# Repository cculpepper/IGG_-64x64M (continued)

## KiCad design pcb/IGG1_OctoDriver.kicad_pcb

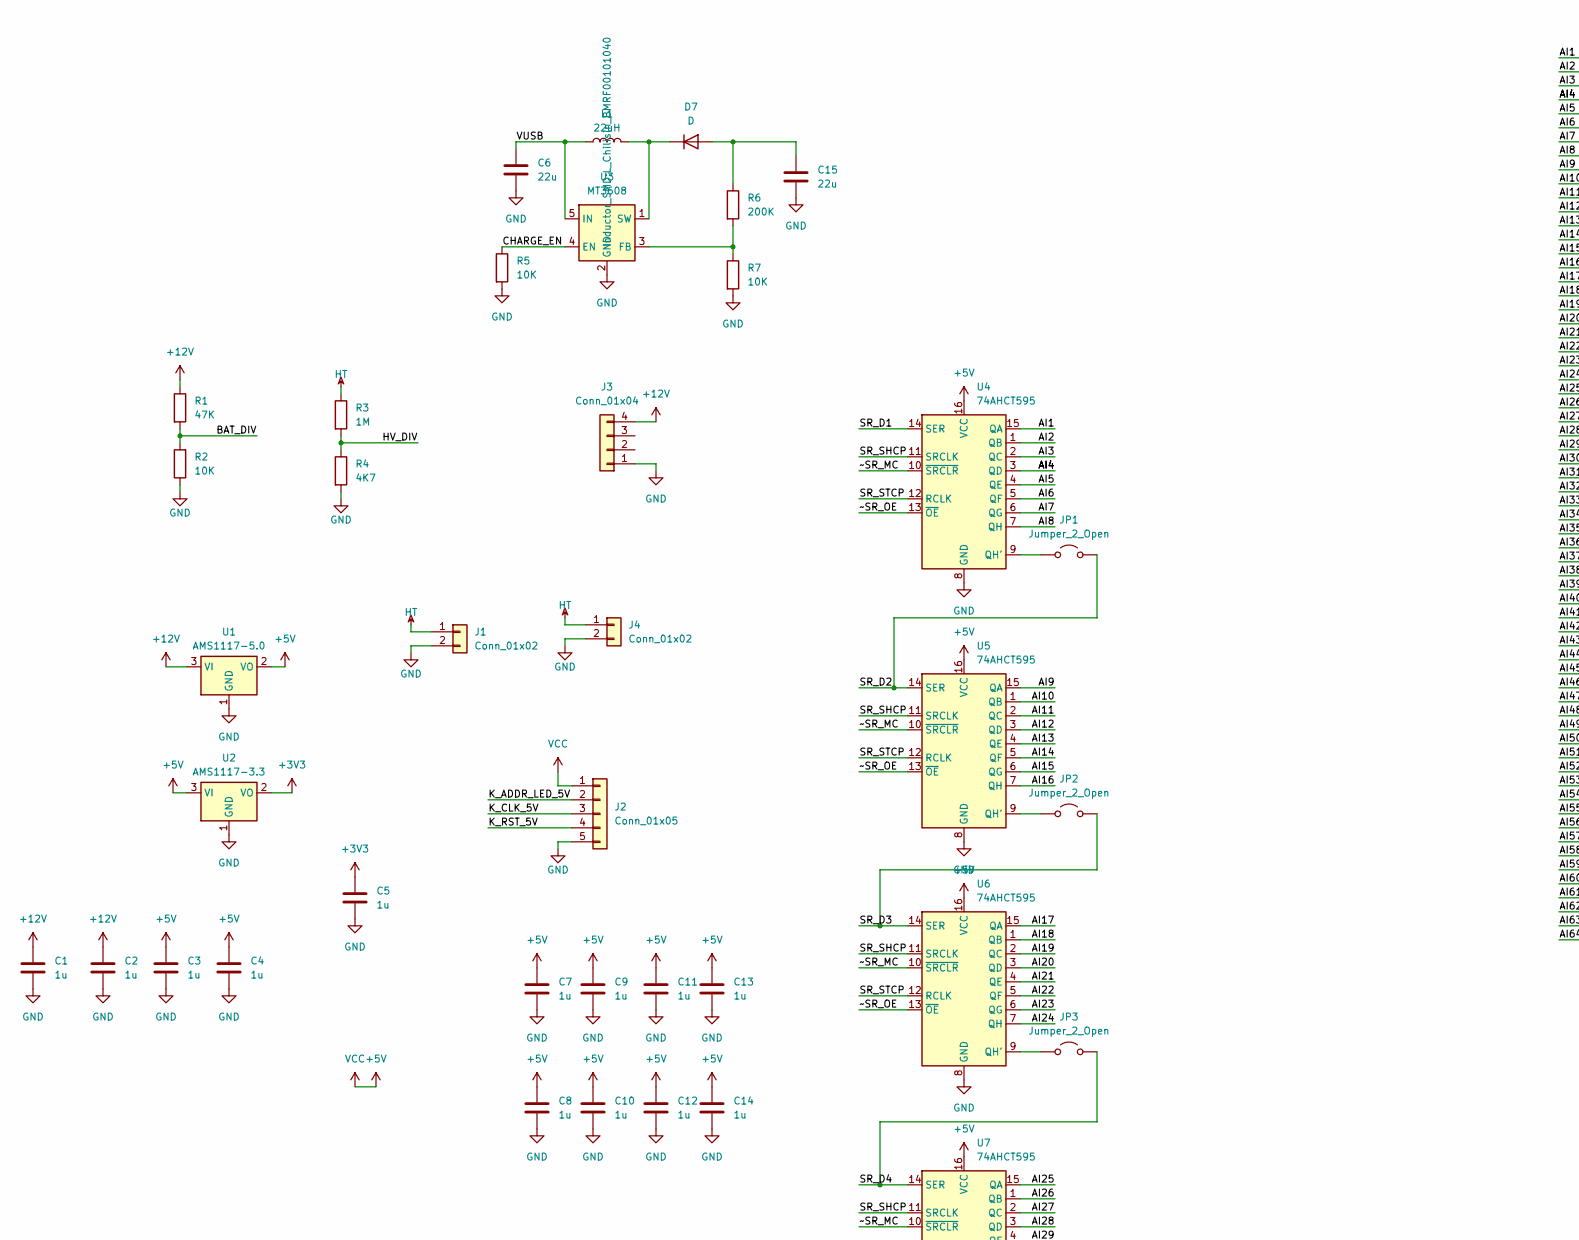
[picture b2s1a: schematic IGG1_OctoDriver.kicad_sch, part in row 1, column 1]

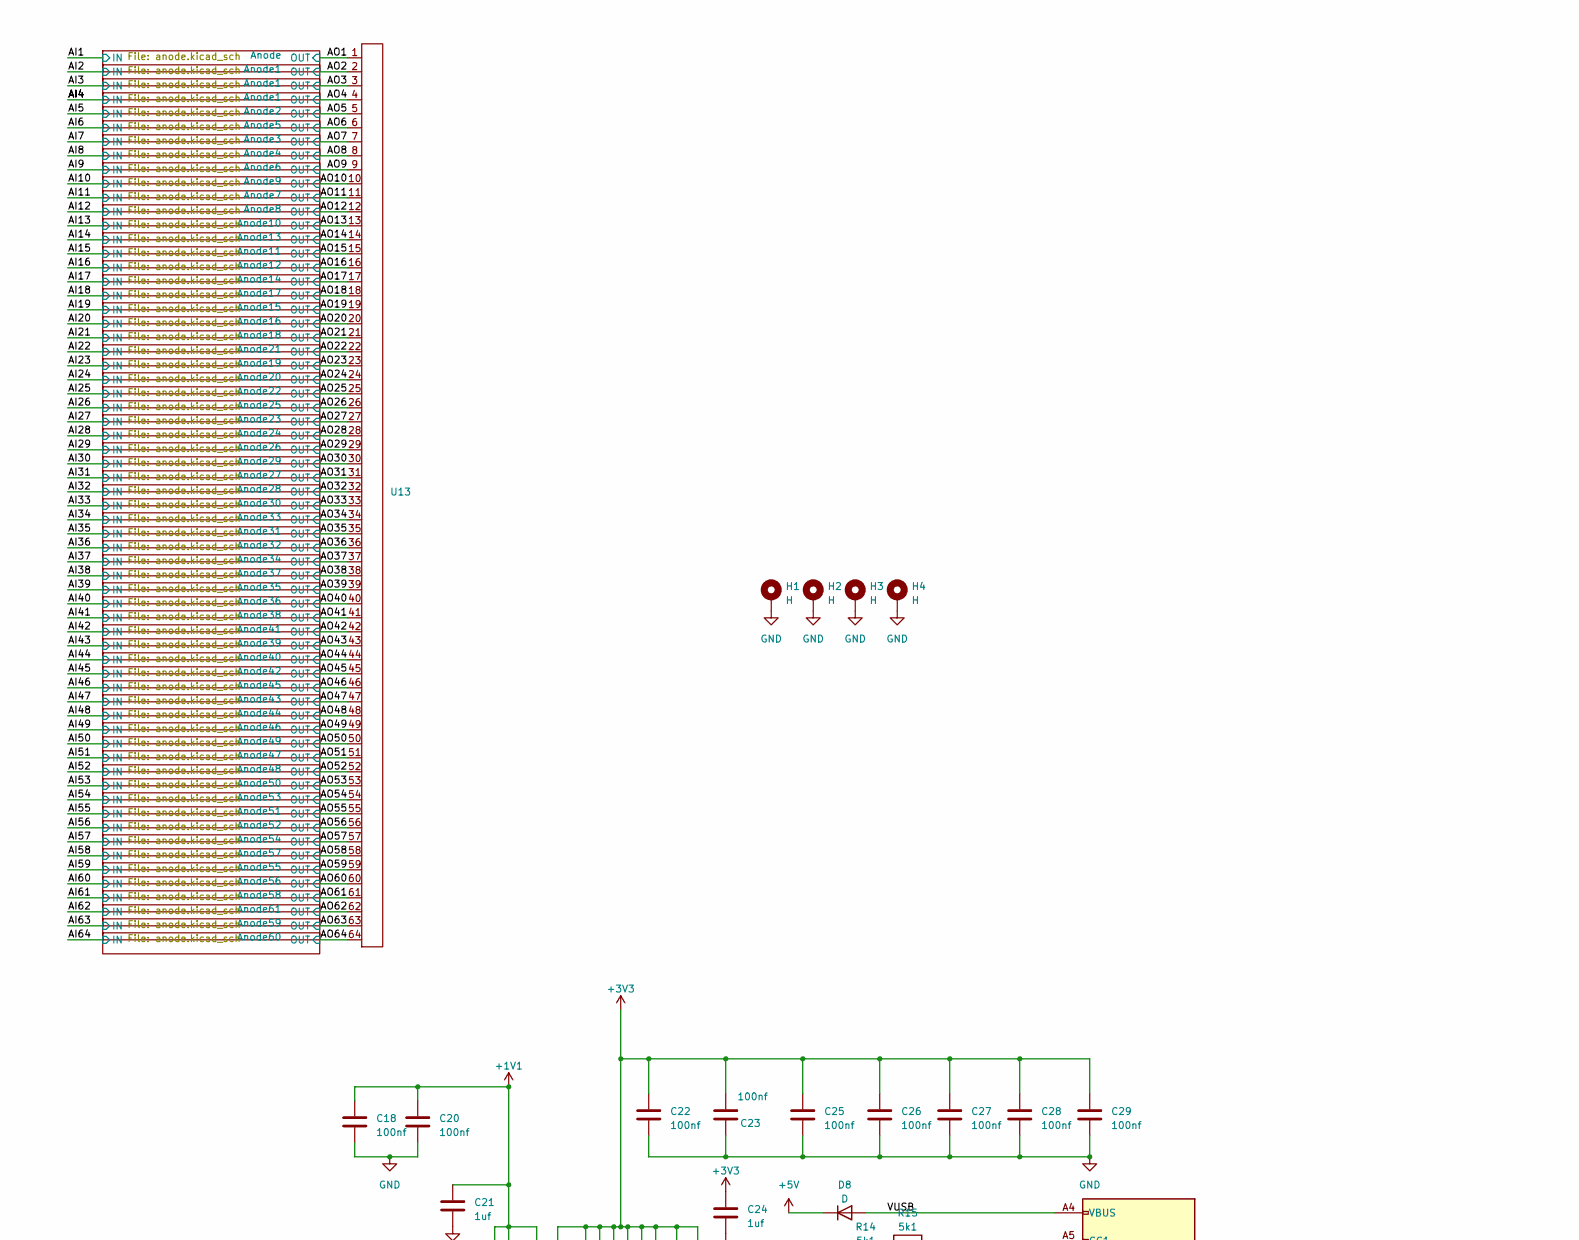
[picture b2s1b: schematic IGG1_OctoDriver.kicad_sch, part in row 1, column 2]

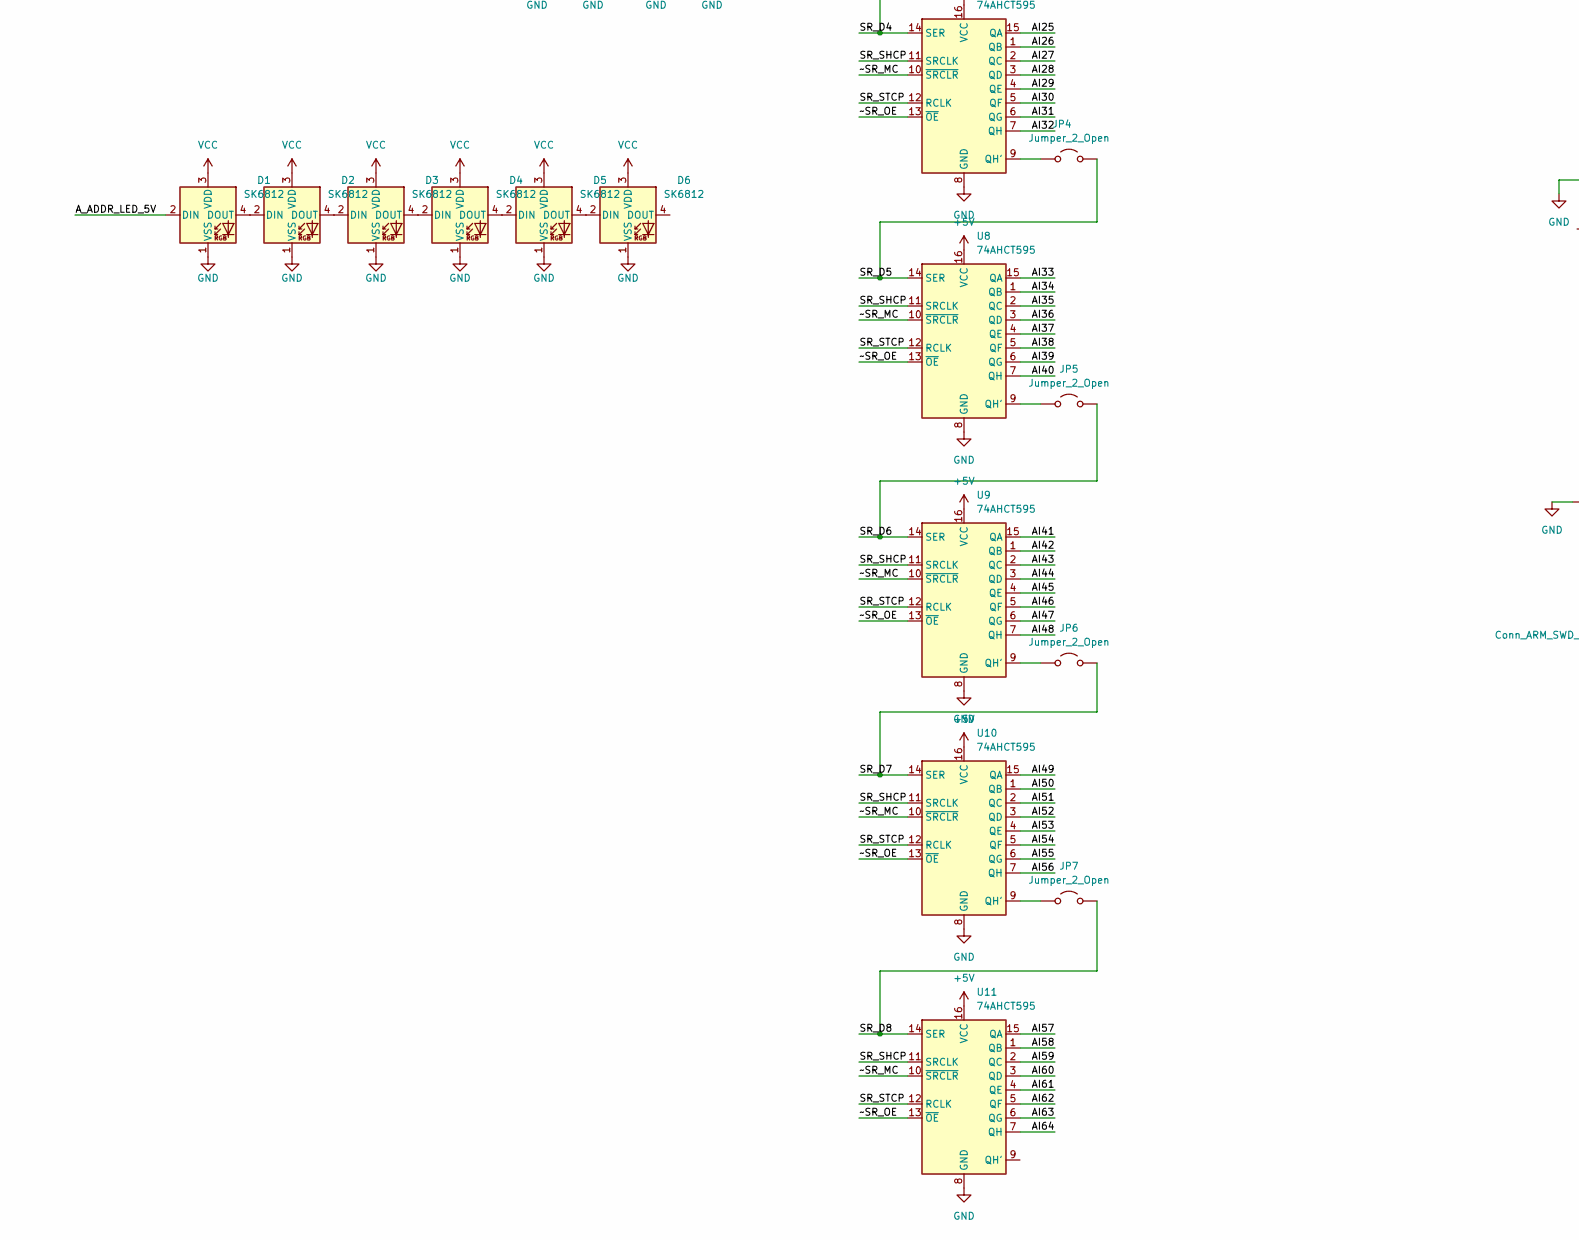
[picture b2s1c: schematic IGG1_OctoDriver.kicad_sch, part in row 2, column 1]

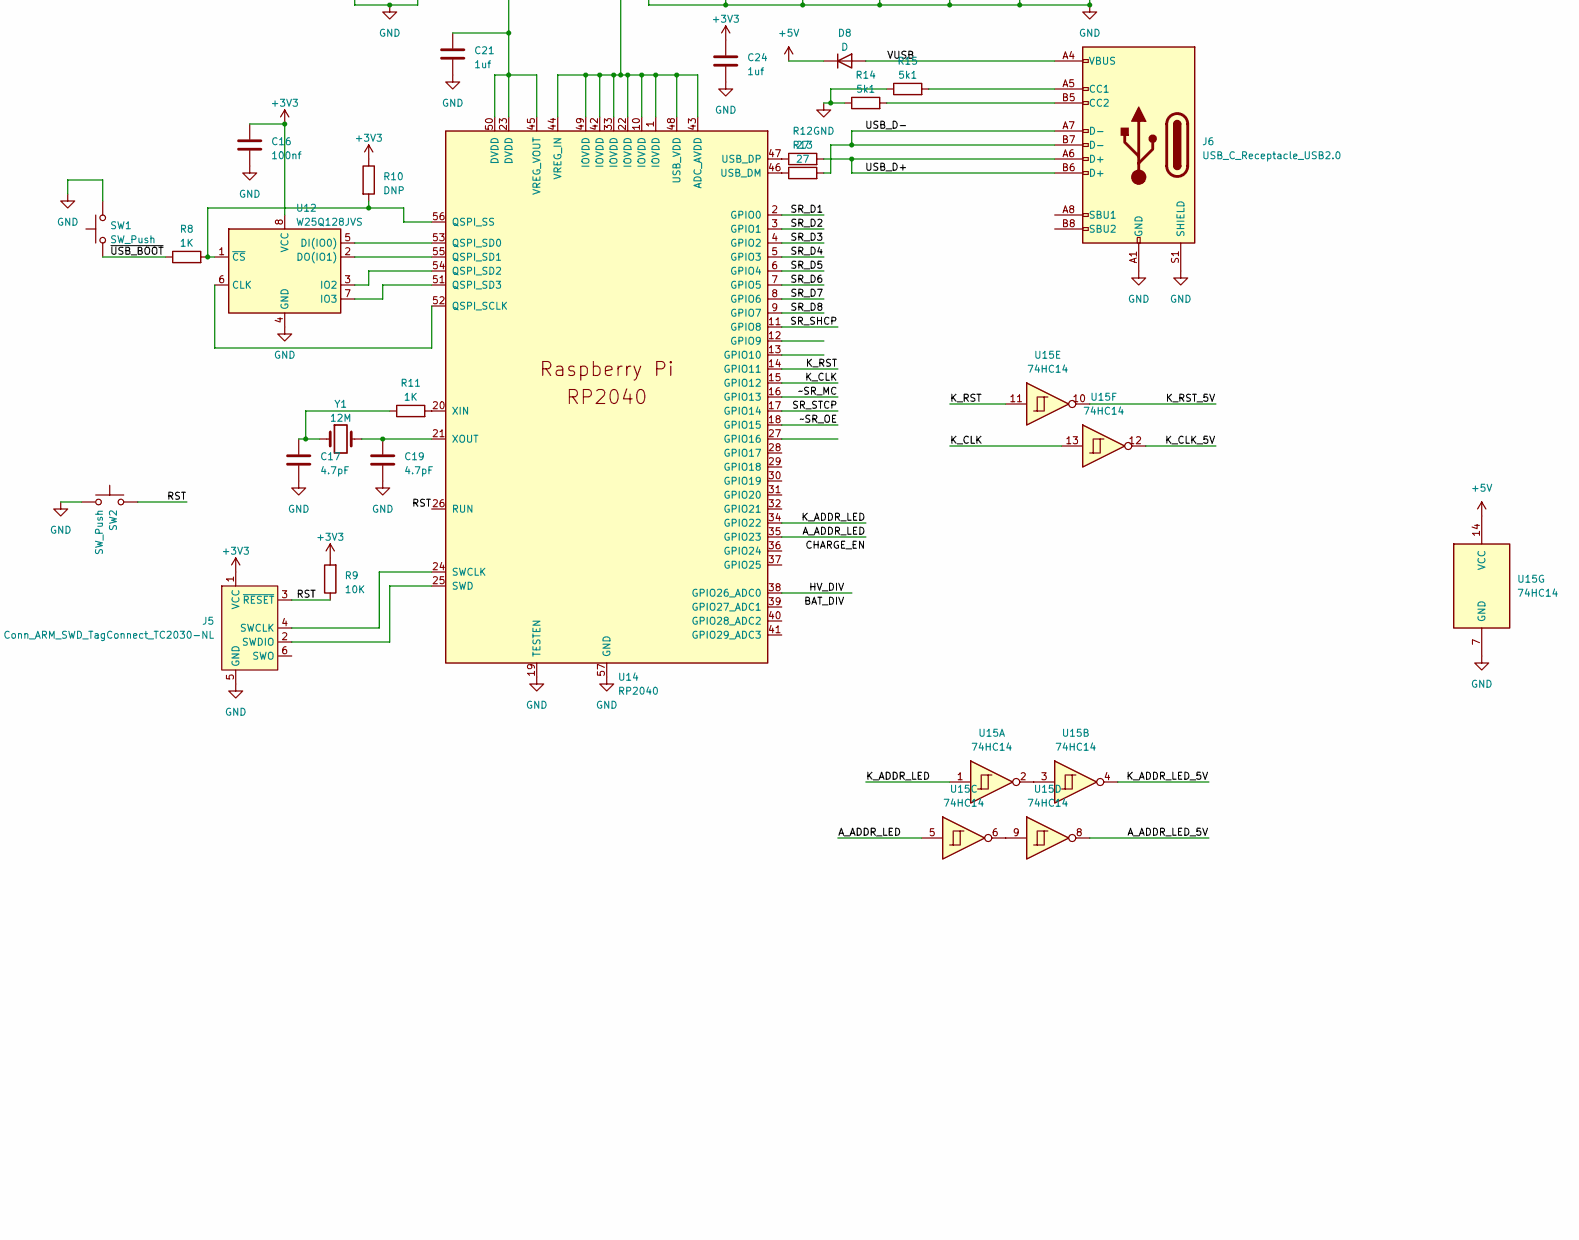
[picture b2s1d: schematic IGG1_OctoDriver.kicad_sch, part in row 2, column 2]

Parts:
C1, C2, C3, C4, C5, C7, C8, C9, C10, C11, C12, C13, C14: 1u; C_0603_1608Metric; LCSC C15849
C6, C15: 22u; C_1206_3216Metric; LCSC C12891
C16, C18, C20, C22, C23, C25, C26, C27, C28, C29: 100nf; C_0603_1608Metric; LCSC C14663
C17, C19: 4.7pF; C_0603_1608Metric; LCSC C1669
C21, C24: 1uf; C_0603_1608Metric; LCSC C15849
D1, D2, D3, D4, D5, D6: SK6812; LED_SK6812MINI_PLCC4_3.5x3.5mm_P1.75mm; LCSC C2922787
D7, D8: D; D_SMA; LCSC C22452
H1, H2, H3, H4: H; MountingHole_3.2mm_M3_DIN965_Pad
J1, J4: Conn_01x02; JST_XH_B2B-XH-AM_1x02_P2.50mm_Vertical
J2: Conn_01x05; JST_XH_B5B-XH-AM_1x05_P2.50mm_Vertical
J3: Conn_01x04; JST_XH_B4B-XH-AM_1x04_P2.50mm_Vertical
J5: Conn_ARM_SWD_TagConnect_TC2030-NL; Tag-Connect_TC2030-IDC-NL_2x03_P1.27mm_Vertical
J6: USB_C_Receptacle_USB2.0; USB_C_Receptacle_HRO_TYPE-C-31-M-12; LCSC C165948
JP1, JP2, JP3, JP4, JP5, JP6, JP7: Jumper_2_Open; SolderJumper-2_P1.3mm_Open_TrianglePad1.0x1.5mm
L1: 22uH; L_Chilisin_BMRF00101040; LCSC C6364679
R1: 47K; R_0603_1608Metric
R2: 10K; R_0603_1608Metric; LCSC C21190
R3: 1M; R_1206_3216Metric; LCSC C17927
R4: 4K7; R_0603_1608Metric; LCSC C23162
R5, R7, R9: 10K; R_0603_1608Metric; LCSC C25804
R6: 200K; R_0603_1608Metric; LCSC C25811
R8, R11: 1K; R_0603_1608Metric; LCSC C21190
R10: DNP; R_0603_1608Metric
R12, R13: 27; R_0603_1608Metric; LCSC C25190
R14, R15: 5k1; R_0603_1608Metric; LCSC C23186
SW1, SW2: SW_Push; SW_SPST_TL3342; LCSC C318884
U1: AMS1117-5.0; SOT-223-3_TabPin2; LCSC C6187
U2: AMS1117-3.3; SOT-223-3_TabPin2
U3: MT3608; SOT-23-6; LCSC C84817
U4, U5, U6, U7, U8, U9, U10, U11: 74AHCT595; SOIC-16_3.9x9.9mm_P1.27mm; LCSC C5947
U12: W25Q128JVS; SOIC-8_5.23x5.23mm_P1.27mm; LCSC C97521
U13: IGG1-Anode
U14: RP2040; QFN-56-1EP_7x7mm_P0.4mm_EP3.2x3.2mm; LCSC C2040
U15: 74HC14; SOIC-14_3.9x8.7mm_P1.27mm; LCSC C5605
Y1: 12M; Crystal_SMD_5032-2Pin_5.0x3.2mm; LCSC C90884

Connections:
+1V1: C18.1, C20.1, C21.1, U14.23 (DVDD), U14.45 (VREG_VOUT), U14.50 (DVDD)
+3V3: C5.1, C16.1, C22.1, C23.1, C24.1, C25.1, C26.1, C27.1, C28.1, C29.1, J5.1 (VCC), R9.2, R10.1, U2.2 (VO), U12.8 (VCC), U14.1 (IOVDD), U14.10 (IOVDD), U14.22 (IOVDD), U14.33 (IOVDD), U14.42 (IOVDD), U14.43 (ADC_AVDD), U14.44 (VREG_IN), U14.48 (USB_VDD), U14.49 (IOVDD)
+5V: C3.1, C4.1, C7.1, C8.1, C9.1, C10.1, C11.1, C12.1, C13.1, C14.1, D1.3 (VDD), D2.3 (VDD), D3.3 (VDD), D4.3 (VDD), D5.3 (VDD), D6.3 (VDD), D8.1 (K), J2.1, U1.2 (VO), U2.3 (VI), U4.16 (VCC), U5.16 (VCC), U6.16 (VCC), U7.16 (VCC), U8.16 (VCC), U9.16 (VCC), U10.16 (VCC), U11.16 (VCC), U15.14 (VCC)
+12V: C1.1, C2.1, J3.4, R1.1, U1.3 (VI)
/AI1: U4.15 (QA); also elsewhere on the board
/AI2: U4.1 (QB); also elsewhere on the board
/AI3: U4.2 (QC); also elsewhere on the board
/AI4: U4.3 (QD); also elsewhere on the board
/AI5: U4.4 (QE); also elsewhere on the board
/AI6: U4.5 (QF); also elsewhere on the board
/AI7: U4.6 (QG); also elsewhere on the board
/AI8: U4.7 (QH); also elsewhere on the board
/AI9: U5.15 (QA); also elsewhere on the board
/AI10: U5.1 (QB); also elsewhere on the board
/AI11: U5.2 (QC); also elsewhere on the board
/AI12: U5.3 (QD); also elsewhere on the board
/AI13: U5.4 (QE); also elsewhere on the board
/AI14: U5.5 (QF); also elsewhere on the board
/AI15: U5.6 (QG); also elsewhere on the board
/AI16: U5.7 (QH); also elsewhere on the board
/AI17: U6.15 (QA); also elsewhere on the board
/AI18: U6.1 (QB); also elsewhere on the board
/AI19: U6.2 (QC); also elsewhere on the board
/AI20: U6.3 (QD); also elsewhere on the board
/AI21: U6.4 (QE); also elsewhere on the board
/AI22: U6.5 (QF); also elsewhere on the board
/AI23: U6.6 (QG); also elsewhere on the board
/AI24: U6.7 (QH); also elsewhere on the board
/AI25: U7.15 (QA); also elsewhere on the board
/AI26: U7.1 (QB); also elsewhere on the board
/AI27: U7.2 (QC); also elsewhere on the board
/AI28: U7.3 (QD); also elsewhere on the board
/AI29: U7.4 (QE); also elsewhere on the board
/AI30: U7.5 (QF); also elsewhere on the board
/AI31: U7.6 (QG); also elsewhere on the board
/AI32: U7.7 (QH); also elsewhere on the board
/AI33: U8.15 (QA); also elsewhere on the board
/AI34: U8.1 (QB); also elsewhere on the board
/AI35: U8.2 (QC); also elsewhere on the board
/AI36: U8.3 (QD); also elsewhere on the board
/AI37: U8.4 (QE); also elsewhere on the board
/AI38: U8.5 (QF); also elsewhere on the board
/AI39: U8.6 (QG); also elsewhere on the board
/AI40: U8.7 (QH); also elsewhere on the board
/AI41: U9.15 (QA); also elsewhere on the board
/AI42: U9.1 (QB); also elsewhere on the board
/AI43: U9.2 (QC); also elsewhere on the board
/AI44: U9.3 (QD); also elsewhere on the board
/AI45: U9.4 (QE); also elsewhere on the board
/AI46: U9.5 (QF); also elsewhere on the board
/AI47: U9.6 (QG); also elsewhere on the board
/AI48: U9.7 (QH); also elsewhere on the board
/AI49: U10.15 (QA); also elsewhere on the board
/AI50: U10.1 (QB); also elsewhere on the board
/AI51: U10.2 (QC); also elsewhere on the board
/AI52: U10.3 (QD); also elsewhere on the board
/AI53: U10.4 (QE); also elsewhere on the board
/AI54: U10.5 (QF); also elsewhere on the board
/AI55: U10.6 (QG); also elsewhere on the board
/AI56: U10.7 (QH); also elsewhere on the board
/AI57: U11.15 (QA); also elsewhere on the board
/AI58: U11.1 (QB); also elsewhere on the board
/AI59: U11.2 (QC); also elsewhere on the board
/AI60: U11.3 (QD); also elsewhere on the board
/AI61: U11.4 (QE); also elsewhere on the board
/AI62: U11.5 (QF); also elsewhere on the board
/AI63: U11.6 (QG); also elsewhere on the board
/AI64: U11.7 (QH); also elsewhere on the board
/AO1: U13.1; also elsewhere on the board
/AO2: U13.2; also elsewhere on the board
/AO3: U13.3; also elsewhere on the board
/AO4: U13.4; also elsewhere on the board
/AO5: U13.5; also elsewhere on the board
/AO6: U13.6; also elsewhere on the board
/AO7: U13.7; also elsewhere on the board
/AO8: U13.8; also elsewhere on the board
/AO9: U13.9; also elsewhere on the board
/AO10: U13.10; also elsewhere on the board
/AO11: U13.11; also elsewhere on the board
/AO12: U13.12; also elsewhere on the board
/AO13: U13.13; also elsewhere on the board
/AO14: U13.14; also elsewhere on the board
/AO15: U13.15; also elsewhere on the board
/AO16: U13.16; also elsewhere on the board
/AO17: U13.17; also elsewhere on the board
/AO18: U13.18; also elsewhere on the board
/AO19: U13.19; also elsewhere on the board
/AO20: U13.20; also elsewhere on the board
/AO21: U13.21; also elsewhere on the board
/AO22: U13.22; also elsewhere on the board
/AO23: U13.23; also elsewhere on the board
/AO24: U13.24; also elsewhere on the board
/AO25: U13.25; also elsewhere on the board
/AO26: U13.26; also elsewhere on the board
/AO27: U13.27; also elsewhere on the board
/AO28: U13.28; also elsewhere on the board
/AO29: U13.29; also elsewhere on the board
/AO30: U13.30; also elsewhere on the board
/AO31: U13.31; also elsewhere on the board
/AO32: U13.32; also elsewhere on the board
/AO33: U13.33; also elsewhere on the board
/AO34: U13.34; also elsewhere on the board
/AO35: U13.35; also elsewhere on the board
/AO36: U13.36; also elsewhere on the board
/AO37: U13.37; also elsewhere on the board
/AO38: U13.38; also elsewhere on the board
/AO39: U13.39; also elsewhere on the board
/AO40: U13.40; also elsewhere on the board
/AO41: U13.41; also elsewhere on the board
/AO42: U13.42; also elsewhere on the board
/AO43: U13.43; also elsewhere on the board
/AO44: U13.44; also elsewhere on the board
/AO45: U13.45; also elsewhere on the board
/AO46: U13.46; also elsewhere on the board
/AO47: U13.47; also elsewhere on the board
/AO48: U13.48; also elsewhere on the board
/AO49: U13.49; also elsewhere on the board
/AO50: U13.50; also elsewhere on the board
/AO51: U13.51; also elsewhere on the board
/AO52: U13.52; also elsewhere on the board
/AO53: U13.53; also elsewhere on the board
/AO54: U13.54; also elsewhere on the board
/AO55: U13.55; also elsewhere on the board
/AO56: U13.56; also elsewhere on the board
/AO57: U13.57; also elsewhere on the board
/AO58: U13.58; also elsewhere on the board
/AO59: U13.59; also elsewhere on the board
/AO60: U13.60; also elsewhere on the board
/AO61: U13.61; also elsewhere on the board
/AO62: U13.62; also elsewhere on the board
/AO63: U13.63; also elsewhere on the board
/AO64: U13.64; also elsewhere on the board
/A_ADDR_LED: U14.35 (GPIO23), U15.5
/A_ADDR_LED_5V: D1.2 (DIN), U15.8
/BAT_DIV: R1.2, R2.2
/CHARGE_EN: R5.1, U3.4 (EN)
/HV_DIV: R3.2, R4.1, U14.38 (GPIO26_ADC0)
/K_ADDR_LED: U14.34 (GPIO22), U15.1
/K_ADDR_LED_5V: J2.2, U15.4
/K_CLK: U14.15 (GPIO12), U15.13
/K_CLK_5V: J2.3, U15.12
/K_RST: U14.14 (GPIO11), U15.11
/K_RST_5V: J2.4, U15.10
/RST: J5.3 (~RESET), R9.1, SW2.2, U14.26 (RUN)
/SR_D1: U4.14 (SER), U14.2 (GPIO0)
/SR_D2: JP1.2 (B), U5.14 (SER), U14.3 (GPIO1)
/SR_D3: JP2.2 (B), U6.14 (SER), U14.4 (GPIO2)
/SR_D4: JP3.2 (B), U7.14 (SER), U14.5 (GPIO3)
/SR_D5: JP4.2 (B), U8.14 (SER), U14.6 (GPIO4)
/SR_D6: JP5.2 (B), U9.14 (SER), U14.7 (GPIO5)
/SR_D7: JP6.2 (B), U10.14 (SER), U14.8 (GPIO6)
/SR_D8: JP7.2 (B), U11.14 (SER), U14.9 (GPIO7)
/SR_SHCP: U4.11 (SRCLK), U5.11 (SRCLK), U6.11 (SRCLK), U7.11 (SRCLK), U8.11 (SRCLK), U9.11 (SRCLK), U10.11 (SRCLK), U11.11 (SRCLK), U14.11 (GPIO8)
/SR_STCP: U4.12 (RCLK), U5.12 (RCLK), U6.12 (RCLK), U7.12 (RCLK), U8.12 (RCLK), U9.12 (RCLK), U10.12 (RCLK), U11.12 (RCLK), U14.17 (GPIO14)
/USB_D+: J6.A6 (D+), J6.B6 (D+), R12.2
/USB_D-: J6.A7 (D-), J6.B7 (D-), R13.2
/VUSB: C6.1, D8.2 (A), J6.A4 (VBUS), J6.A9 (VBUS), J6.B4 (VBUS), J6.B9 (VBUS), L1.1, U3.5 (IN)
/~SR_MC: U4.10 (~SRCLR), U5.10 (~SRCLR), U6.10 (~SRCLR), U7.10 (~SRCLR), U8.10 (~SRCLR), U9.10 (~SRCLR), U10.10 (~SRCLR), U11.10 (~SRCLR), U14.16 (GPIO13)
/~SR_OE: U4.13 (~OE), U5.13 (~OE), U6.13 (~OE), U7.13 (~OE), U8.13 (~OE), U9.13 (~OE), U10.13 (~OE), U11.13 (~OE), U14.18 (GPIO15)
/~USB_BOOT: R8.1, SW1.1
GND: C1.2, C2.2, C3.2, C4.2, C5.2, C6.2, C7.2, C8.2, C9.2, C10.2, C11.2, C12.2, C13.2, C14.2, C15.2, C16.2, C17.2, C18.2, C19.2, C20.2, C21.2, C22.2, C23.2, C24.2, C25.2, C26.2, C27.2, C28.2, C29.2, D1.1 (VSS), D2.1 (VSS), D3.1 (VSS), D4.1 (VSS), D5.1 (VSS), D6.1 (VSS), H1.1, H2.1, H3.1, H4.1, J1.2, J2.5, J3.1, J4.2, J5.5 (GND), J6.A1 (GND), J6.A12 (GND), J6.B1 (GND), J6.B12 (GND), J6.S1 (SHIELD), R2.1, R4.2, R5.2, R7.2, R14.1, R15.1, SW1.2, SW2.1, U1.1 (GND), U2.1 (GND), U3.2 (GND), U4.8 (GND), U5.8 (GND), U6.8 (GND), U7.8 (GND), U8.8 (GND), U9.8 (GND), U10.8 (GND), U11.8 (GND), U12.4 (GND), U14.19 (TESTEN), U14.57 (GND), U15.7 (GND); also elsewhere on the board
HT: J1.1, J4.1, R3.1; also elsewhere on the board
unnamed: C17.1, R11.1, Y1.1
unnamed: D1.4 (DOUT), D2.2 (DIN)
unnamed: D2.4 (DOUT), D3.2 (DIN)
unnamed: D3.4 (DOUT), D4.2 (DIN)
unnamed: D4.4 (DOUT), D5.2 (DIN)
unnamed: D5.4 (DOUT), D6.2 (DIN)
unnamed: C15.1, D7.2 (A), R6.1
unnamed: D7.1 (K), L1.2, U3.1 (SW)
unnamed: J5.4 (SWCLK), U14.24 (SWCLK)
unnamed: J5.2 (SWDIO), U14.25 (SWD)
unnamed: J6.A5 (CC1), R15.2
unnamed: J6.B5 (CC2), R14.2
unnamed: JP1.1 (A), U4.9 (QH')
unnamed: JP2.1 (A), U5.9 (QH')
unnamed: JP3.1 (A), U6.9 (QH')
unnamed: JP4.1 (A), U7.9 (QH')
unnamed: JP5.1 (A), U8.9 (QH')
unnamed: JP6.1 (A), U9.9 (QH')
unnamed: JP7.1 (A), U10.9 (QH')
unnamed: R6.2, R7.1, U3.3 (FB)
unnamed: U12.6 (CLK), U14.52 (QSPI_SCLK)
unnamed: U12.5 (DI(IO0)), U14.53 (QSPI_SD0)
unnamed: U12.2 (DO(IO1)), U14.55 (QSPI_SD1)
unnamed: U12.3 (IO2), U14.54 (QSPI_SD2)
unnamed: U12.7 (IO3), U14.51 (QSPI_SD3)
unnamed: R8.2, R10.2, U12.1 (~CS), U14.56 (QSPI_SS)
unnamed: R13.1, U14.46 (USB_DM)
unnamed: R12.1, U14.47 (USB_DP)
unnamed: R11.2, U14.20 (XIN)
unnamed: C19.1, U14.21 (XOUT), Y1.2
unnamed: U15.2, U15.3
unnamed: U15.6, U15.9
